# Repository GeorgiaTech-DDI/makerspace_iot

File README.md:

# [Makerspace IoT (MSIoT)](https://github.com/GeorgiaTech-DDI/makerspace_iot/wiki)

Makerspace IoT is a sub-project of the Smart^3 Makerspaces Vertically Integrated Project, aiming to digitalize and provide actionable insights for machines in the Flowers Invention Studio.

This is achieved using sensors which continuously collect data on various parameters (current, vibration, temperature) for a machine. The project aims to create a one-of-a-kind low-cost, scalable IoT infrastructure which aids in the **predictive maintenance** of the machinery.

This wiki provides more in-depth documentation of the resources utilized in the project.

## [Introduction and Onboarding](https://github.com/GeorgiaTech-DDI/makerspace_iot/wiki/Quickstart-Guide-(Read-me-first!))
💡*What impact does this project create? How does this contribute to the existing IoT and predictive maintenance research?*

➡️**Aim of the project** <br /> Enable data collection for various machine parameters in Flower Invention Studio.

➡️**Research gap identified** <br /> After going through various research papers we realised there was no paper which holistically combines principles of mechanical, electrical, electronics and computer science to setup predictive maintenance ..............

➡️**Work done:** <br /> We have made an IoT infrastructure which utilizes sensors to gather data on various machine parameters like current, vibration, temperature etc. These machine parameters are constantly measured and stored in a cloud warehouse. 

➡️**Impact created** <br />
This data stored can be utilized in 2 ways:-
1. Live visualization: An app can be created that displays a live dashboard showcasing real-time values of the current, vibration and temperature. This can be utilized in small-medium sized industrial setups which till now have not modernized their machinery. The low cost of our infrastructure can help bring these sectors online.

2. **Predictive maintenance:** As discussed in the *research gap* part, in the present scenario only industries with high capital are able to utilize sensor-based predictive maintenance techniques for their machines.

➡️**Result** <br />
After this research project, we will have documentation that talks about an end-to-end method to enable predictive maintenance for any machine in the industry, from **sensor selection -> Circuitry -> Cloud infrastructure -> Data collection procedures -> Data manipulation and insights**. After reading the documentation anyone can set up a predictive maintenance infrastructure without requiring any prior experience with the same. 

[**✅Click here**](https://github.com/GeorgiaTech-DDI/makerspace_iot/wiki/Quickstart-Guide-(Read-me-first!)) **to get a quickstart guide and detailed info about project goals, teams, hardware & software used and much more..!**

## [Documentation](https://github.com/GeorgiaTech-DDI/makerspace_iot/wiki)

MSIoT documents, setups, and details on progress.

## Point Of Contacts 
**MSIoT Lead** <br />
👨‍💻 Rahul Gupta (Computer Engineer Undergraduate) <br />
📍 Atlanta, Georgia <br />
📧 rgupta451@gatech.edu <br />
🔗 https://www.linkedin.com/in/rah-gupta/ <br />

**AWS Lead** <br />
👨‍💻 Connor Priest (Computer Engineer Undergraduate) <br />
📍 Atlanta, Georgia <br />
📧 cpriest7@gatech.edu <br />
🔗 https://www.linkedin.com/in/connor-priest-772954220 <br />

**MSIoT Lead** <br />
👨‍💻 Gate Tangchartsiri (Computer Engineer Undergraduate) <br />
📍 Atlanta, Georgia <br />
📧 gate.tang@gatech.edu <br />
🔗 www.linkedin.com/in/gate-tangchartsiri/ <br />

**Team Lead - Analytics** <br />
👨‍💻 Aditya Jarial (Mechanical Engineering Researcher at Georgia Tech) <br />
📍 Gurugram, India <br />
📧 mr.adityasingh99@gmail.com <br />
🔗 www.linkedin.com/in/aditya-jarial <br />

## Additional Information
[MAC Address Indentifier](https://randomnerdtutorials.com/get-change-esp32-esp8266-mac-address-arduino/)

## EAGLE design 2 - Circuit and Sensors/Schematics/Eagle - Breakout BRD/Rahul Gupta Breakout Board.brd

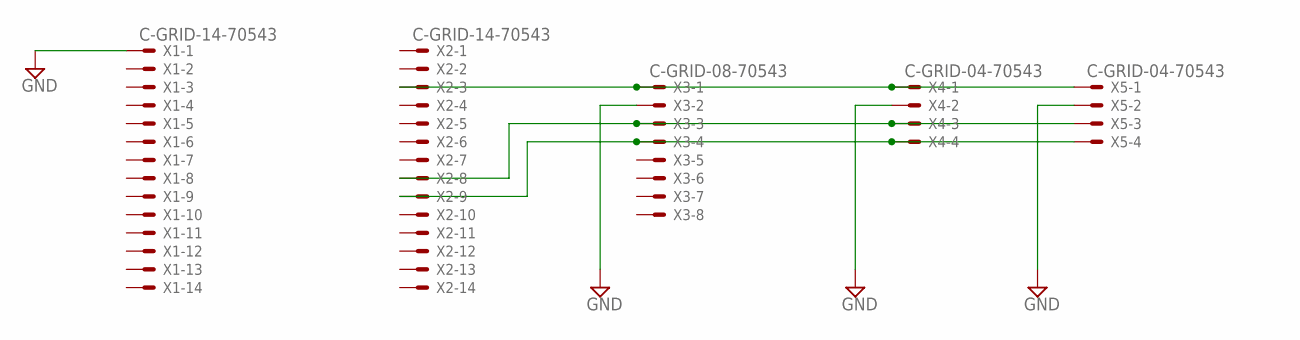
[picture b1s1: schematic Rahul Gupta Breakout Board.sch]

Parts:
X1, X2: C-GRID-14-70543; 70543-14
X3: C-GRID-08-70543; 70543-08
X4, X5: C-GRID-04-70543; 70543-04

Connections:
GND: X1.1, X3.2, X4.2, X5.2
unnamed: X2.3, X3.1, X4.1, X5.1
unnamed: X2.8, X3.3, X4.3, X5.3
unnamed: X2.9, X3.4, X4.4, X5.4

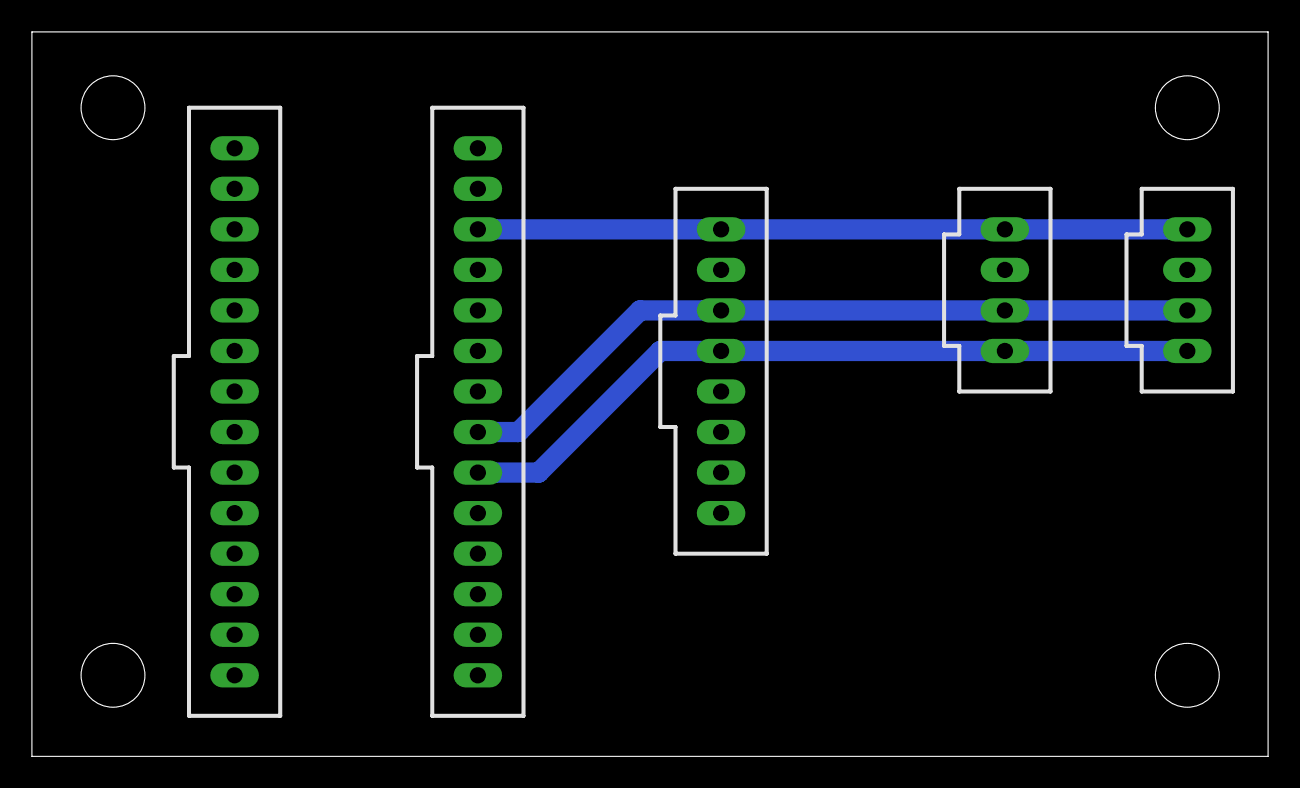
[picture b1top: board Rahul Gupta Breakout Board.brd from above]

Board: 2 copper layers, 77.5 x 45.4 mm, 5 parts (0 on the bottom side), 4 nets.

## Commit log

2022-11-05 Create Flask web app that can read from DynamoDB
2022-11-05 Add support for POSTing data for a specific sensor
2022-11-06 Set up MQTT connection with AWS IoT and publish test messages
2022-11-06 Add documentation and requirements file
2022-11-06 Add other resources to README
2022-11-08 Refactor code and create helper functions for AWS IoT
2022-11-19 Arduino codes for ESP32 added. ESP8266 not used becuase does not support WiFi.h library.
2022-11-19 Redudant current_measurer.ino deleted
2022-11-19 Outdated code only used for references.
2022-11-23 esp32_iot file added. esp8266_iot.ino file used for example.
2022-11-23 Documentation/Tutorial for ESP32 added.
2022-11-23 Images folder added for github wiki and readme.
2022-11-24 Documentation for esp32_iot.ino created and added - 11/24/2022
2022-11-24 Documentation - AWS_setup documentation moved from README.md to aws_setup.md. Compartmentalization started.
2022-11-24 New README.md page added
2022-12-02 Flowchart added to files directory
2022-12-02 Flowchart added to README.md page
2022-12-06 Projects organization Flowchart updated.
2022-12-13 Arduino code for Portenta X8 added
2022-12-13 Portenta Arduino Code changed to include RPC implementation.
2022-12-14 Python script added. Folders regorganized.
2022-12-14 Libraries for python script - RPC added.
2022-12-15 Flowchart updated to match Potenta X8 change.
2022-12-18 Python script for Kasa IP address added.
2022-12-18 Requirements.txt updated.
2022-12-18 kasa.py file added with power readings
2022-12-18 Flowchart updated
2022-12-19 kasa.py file renamed to kasap_script.py
2022-12-19 Comments added
2022-12-19 kasa_script.py updated
2022-12-22 m4_to_python.py file added
2022-12-27 iot box folder added.
2022-12-27 Current Project timeline for first story created.
2022-12-28 iot_box for ardunio IDE code added.
2022-12-28 README.md file updated.
2022-12-28 bbb2aws program added. Program has not been double checked yet.
2022-12-29 flowchart for iot_box image created.
2023-01-02 iot_box roadmap adjusted.
2023-01-04 iot_box teensy code modified to analogRead relay voltage.
2023-01-04 iot_box teensy code syntax fixed.
2023-01-13 iot_box teensy code updated
2023-01-14 Diagram for project flowchart adjusted.
2023-01-22 Project timeline updated.
2023-02-11 README.md file updated
2023-02-11 image for wiki renovations.
2023-02-11 Project timeline switched to Gantt Chart
2023-03-14 Folders reorganized. Fall 22 Work moved to archived folder.
2023-03-18 Node-RED flow added.
2023-03-18 teensy to BBB serial communcation image added.
2023-03-18 Teensy arduino code for printing JSON-formatted data for serial communication.
2023-03-19 Image of IoT core JSON formatting for documentation purposes added
2023-04-27 Lambda Functiono Updated Python Code
2023-04-27 Lambda Function Used in MakerSpace IoT
2023-04-27 Did not put into a folder
    Re Added it to git but now put it into the Spring_23 IoT folder
2023-05-11 Teensy arduino code updated and moved to Spring23 folder.
2023-05-11 fall22_archive folder moved to archived folder.
2023-06-18 Intial MPU6050 Accel and Gyro Code added.
2023-06-18 README page updated to match links and logo added.
2023-06-18 Logo updated to vector svg image
2023-07-03 Initial test MPU6050 CSV dataset added.
2023-07-15 Fan Data for MPU6050 added to sensors folder.
2023-07-22 Updated profile
2023-09-07 Schematics for MPU6050 Circuitry Uploaded.
2023-09-07 Program for Teensy for MPU6050 uploaded.
2023-09-22 Senser Suite Data with Accel & Gyro data added.
2023-09-28 New V2 schematics and full suite code has been added.
2023-10-13 Changed the acc Xs to “AccY” and AccZ respectively
    Update MPU6050_Full_Suite.ino
2023-10-14 Update LambdaFunction.py to new function
2023-10-27 Beagle Bone files added including the serialInit.py and serialToAWS.py file.
2023-11-03 Add software docs in dedicated folder
2023-12-01 Housing and Analytics Push for Fall 2023 Semester
    Housing:
    - Uploaded CAD Files for Fastener Housing which is currently IN USE
    - Uploaded CAD Files for redundant snap fit housing
    Analytics:
    - Uploaded Datasets for all data collected during the Fall 2023 Semester
2023-12-01 Reorganized Folders for Simplicity
2023-12-01 Added Images for Housing Documentation
2024-03-24 add iot core to dynamo db code
    Updated code from previous semeters
2024-03-24 API layers for lambda function
2024-03-24 API query function
2024-09-27 Added network error handling and Teensy connectivity
2024-10-03 Got rid of duplicate values
2024-10-06 Reorganized Repo
2024-10-06 Reorganized Circuit Folder
2024-10-10 Lambda function for IoT box
2024-11-04 Added real date time
2024-11-10 Added housing interface
2024-11-10 Added images for documentation
2025-03-20 Created python script with moving average data
